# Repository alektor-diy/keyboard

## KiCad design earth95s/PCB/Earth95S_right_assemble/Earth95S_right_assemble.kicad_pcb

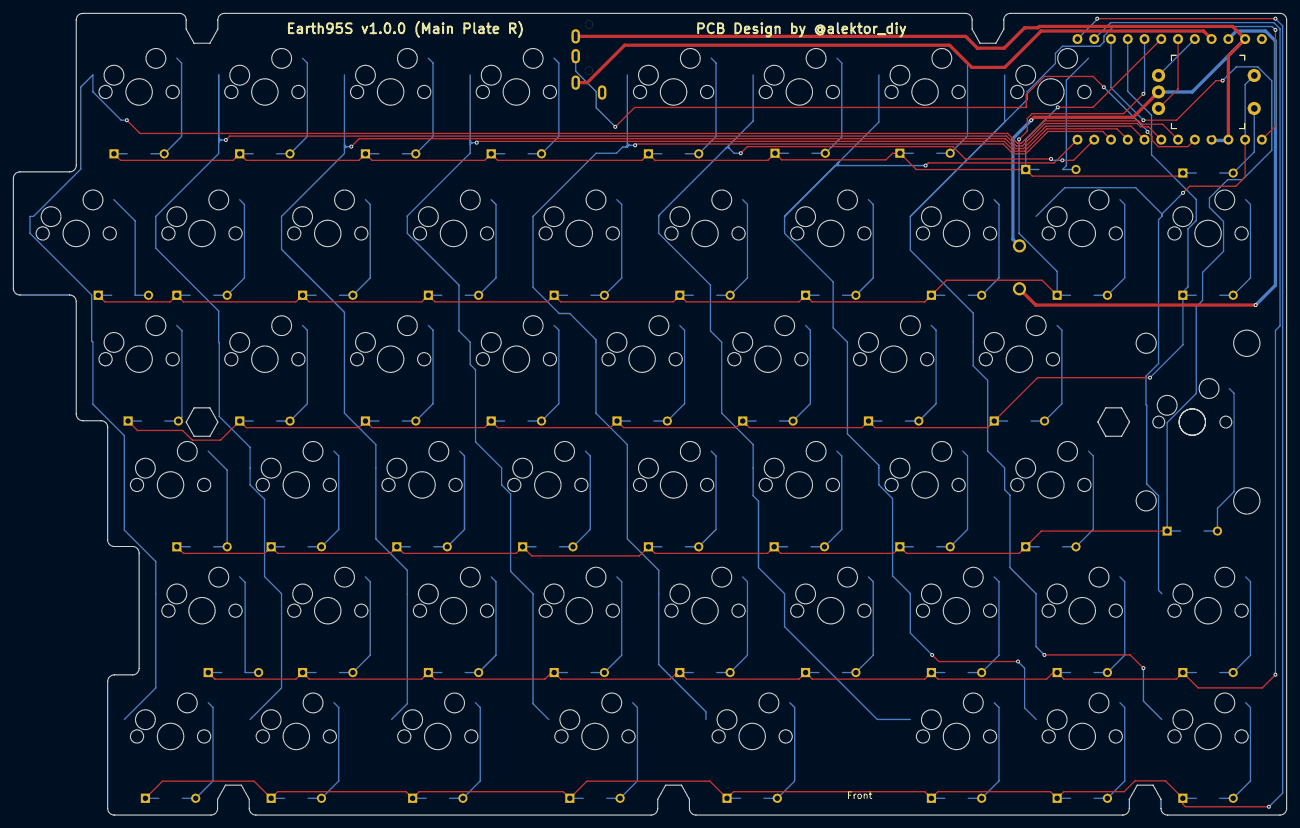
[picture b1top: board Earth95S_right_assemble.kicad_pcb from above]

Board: 2 copper layers, 192.9 x 121.4 mm, 111 parts (1 on the bottom side), 74 nets.

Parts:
D44, D45, D46, D47, D48, D49, D50, D51, D52, D53, D54, D55, D56, D57, D58, D59, D60, D61, D62, D63, D64, D65, D66, D67, D68, D69, D70, D71, D72, D73, D74, D75, D76, D77, D78, D79, D80, D81, D82, D83, D84, D85, D86, D87, D88, D89, D90, D91, D92, D93, D94, D95, D96: D; Diode_TH_SMD
J44: TRRS_MJ-4PP-9
Ref**: Val**; m2_Spacer_Hole_hex
Ref**#2: Val**; m2_Spacer_Hole_hex
SW44, SW45, SW46, SW47, SW48, SW49, SW50, SW51, SW53, SW54, SW55, SW56, SW57, SW58, SW59, SW60, SW61, SW62, SW63, SW64, SW65, SW66, SW67, SW68, SW69, SW70, SW71, SW72, SW73, SW74, SW75, SW76, SW77, SW78, SW80, SW81, SW82, SW83, SW84, SW85, SW86, SW87, SW88, SW89, SW90, SW94, SW95, SW96: SW_PUSH; CherryMX_Hotswap_1u
SW52: RotaryEncoder_Switch; RotaryEncoder_EC12E
SW79: SW_PUSH; CherryMX_Hotswap_ISO
SW91, SW92, SW93: SW_PUSH; CherryMX_Hotswap_1.25u
SW97: SW_PUSH; ResetSW
U44: ProMicro; Micon_ProMicro_reverse

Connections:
Data: J44.C, U44.5 (2/D1/SDA)
GND: J44.B, SW52.C, SW97.2, U44.3 (GND), U44.4 (GND), U44.23 (GND)
unnamed: D44.2 (A), SW44.2
unnamed: D45.2 (A), SW45.2
unnamed: D46.2 (A), SW46.2
unnamed: D47.2 (A), SW47.2
unnamed: D48.2 (A), SW48.2
unnamed: D49.2 (A), SW49.2
unnamed: D50.2 (A), SW50.2
unnamed: D51.2 (A), SW51.2
unnamed: D52.2 (A), SW52.S1
unnamed: D53.2 (A), SW53.2
unnamed: D54.2 (A), SW54.2
unnamed: D55.2 (A), SW55.2
unnamed: D56.2 (A), SW56.2
unnamed: D57.2 (A), SW57.2
unnamed: D58.2 (A), SW58.2
unnamed: D59.2 (A), SW59.2
unnamed: D60.2 (A), SW60.2
unnamed: D61.2 (A), SW61.2
unnamed: D62.2 (A), SW62.2
unnamed: D63.2 (A), SW63.2
unnamed: D64.2 (A), SW64.2
unnamed: D65.2 (A), SW65.2
unnamed: D66.2 (A), SW66.2
unnamed: D67.2 (A), SW67.2
unnamed: D68.2 (A), SW68.2
unnamed: D69.2 (A), SW69.2
unnamed: D70.2 (A), SW70.2
unnamed: D71.2 (A), SW71.2
unnamed: D72.2 (A), SW72.2
unnamed: D73.2 (A), SW73.2
unnamed: D74.2 (A), SW74.2
unnamed: D75.2 (A), SW75.2
unnamed: D76.2 (A), SW76.2
unnamed: D77.2 (A), SW77.2
unnamed: D78.2 (A), SW78.2
unnamed: D79.2 (A), SW79.2
unnamed: D80.2 (A), SW80.2
unnamed: D81.2 (A), SW81.2
unnamed: D82.2 (A), SW82.2
unnamed: D83.2 (A), SW83.2
unnamed: D84.2 (A), SW84.2
unnamed: D85.2 (A), SW85.2
unnamed: D86.2 (A), SW86.2
unnamed: D87.2 (A), SW87.2
unnamed: D88.2 (A), SW88.2
unnamed: D89.2 (A), SW89.2
unnamed: D90.2 (A), SW90.2
unnamed: D91.2 (A), SW91.2
unnamed: D92.2 (A), SW92.2
unnamed: D93.2 (A), SW93.2
unnamed: D94.2 (A), SW94.2
unnamed: D95.2 (A), SW95.2
unnamed: D96.2 (A), SW96.2
RST: SW97.1, U44.22 (RST)
VCC: J44.D, U44.21 (VCC)
col0: SW44.1, SW53.1, SW62.1, SW71.1, SW80.1, SW89.1, U44.6 (3/D0/SCL)
col1: SW45.1, SW54.1, SW63.1, SW72.1, SW81.1, SW90.1, U44.7 (4/D4)
col2: SW46.1, SW55.1, SW64.1, SW73.1, SW82.1, SW91.1, U44.8 (5/C6)
col3: SW47.1, SW56.1, SW65.1, SW74.1, SW83.1, SW92.1, U44.9 (6/D7)
col4: SW48.1, SW57.1, SW66.1, SW75.1, SW84.1, SW93.1, U44.10 (7/E6)
col5: SW49.1, SW58.1, SW67.1, SW76.1, SW85.1, SW94.1, U44.11 (8/B4)
col6: SW50.1, SW59.1, SW68.1, SW77.1, SW86.1, SW95.1, U44.12 (9/B5)
col7: SW51.1, SW60.1, SW69.1, SW78.1, SW87.1, SW96.1, U44.1 (TX0/D3)
col8: SW52.S2, SW61.1, SW70.1, SW79.1, SW88.1, U44.2 (RX1/D2)
re-a: SW52.A, U44.20 (F4/A3)
re-b: SW52.B, U44.19 (F5/A2)
row0: D44.1 (K), D45.1 (K), D46.1 (K), D47.1 (K), D48.1 (K), D49.1 (K), D50.1 (K), D51.1 (K), D52.1 (K), U44.18 (F6/A1)
row1: D53.1 (K), D54.1 (K), D55.1 (K), D56.1 (K), D57.1 (K), D58.1 (K), D59.1 (K), D60.1 (K), D61.1 (K), U44.17 (F7/A0)
row2: D62.1 (K), D63.1 (K), D64.1 (K), D65.1 (K), D66.1 (K), D67.1 (K), D68.1 (K), D69.1 (K), D70.1 (K), U44.16 (B1/15)
row3: D71.1 (K), D72.1 (K), D73.1 (K), D74.1 (K), D75.1 (K), D76.1 (K), D77.1 (K), D78.1 (K), D79.1 (K), U44.15 (B3/14)
row4: D80.1 (K), D81.1 (K), D82.1 (K), D83.1 (K), D84.1 (K), D85.1 (K), D86.1 (K), D87.1 (K), D88.1 (K), U44.14 (B2/16)
row5: D89.1 (K), D90.1 (K), D91.1 (K), D92.1 (K), D93.1 (K), D94.1 (K), D95.1 (K), D96.1 (K), U44.13 (B6/10)
